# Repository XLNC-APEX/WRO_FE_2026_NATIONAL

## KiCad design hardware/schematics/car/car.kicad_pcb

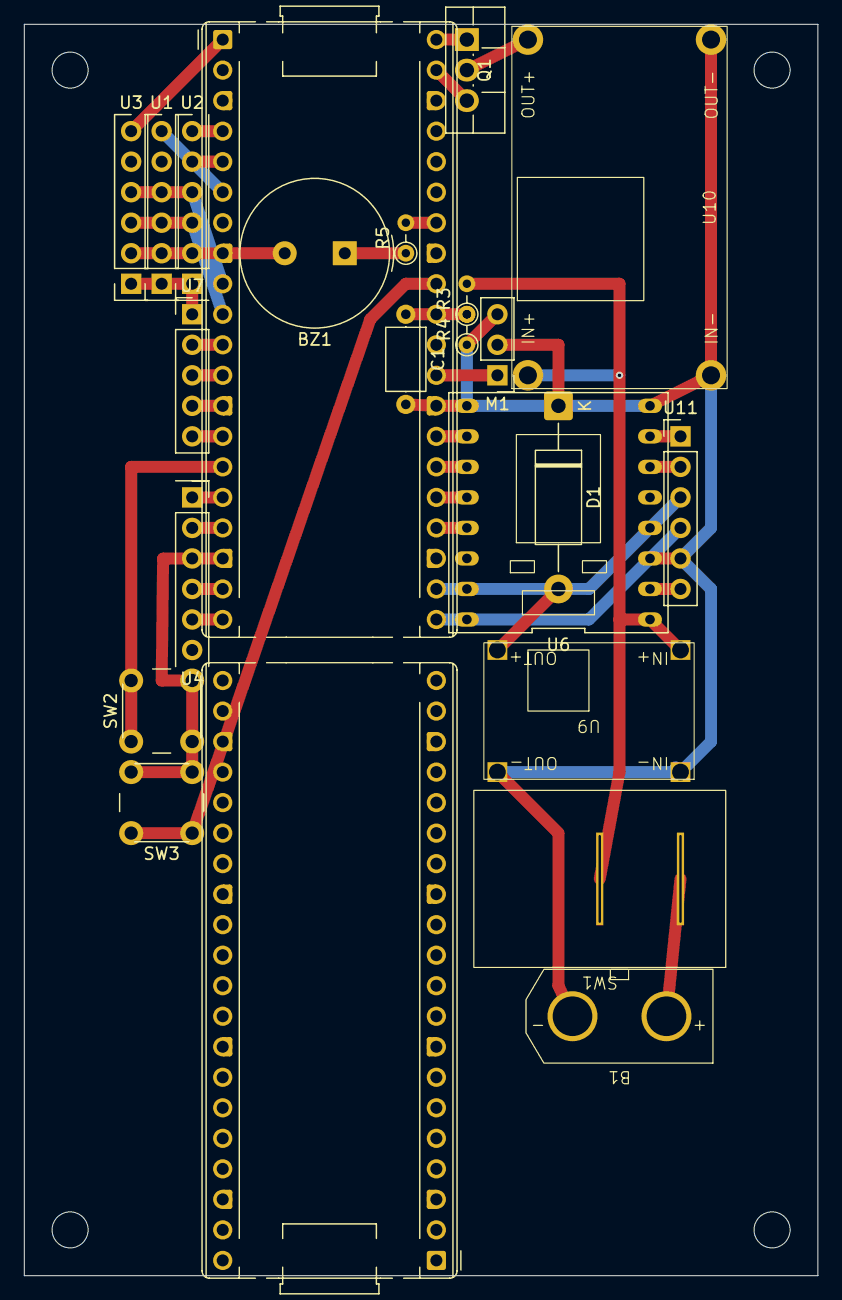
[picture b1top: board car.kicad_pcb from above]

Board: 12 copper layers, 66.0 x 104.1 mm, 23 parts (0 on the bottom side), 38 nets.

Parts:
A1, A1#2: RaspberryPi_Pico2; RaspberryPi_Pico_Common_THT
B1: XT60
BZ1: Buzzer; Buzzer_TDK_PS1240P02BT_D12.2mm_H6.5mm
C1: 1uF; C_Axial_L5.1mm_D3.1mm_P7.50mm_Horizontal
D1: 1N5824; D_DO-15_P15.24mm_Horizontal
M1: Motor_Servo; PinHeader_1x03_P2.54mm_Vertical
Q1: PMOS; TO-220F-3_Vertical
R3: 470k; R_Axial_DIN0204_L3.6mm_D1.6mm_P2.54mm_Vertical
R4: 100k; R_Axial_DIN0204_L3.6mm_D1.6mm_P2.54mm_Vertical
R5: 200; R_Axial_DIN0204_L3.6mm_D1.6mm_P2.54mm_Vertical
SW1: SW_SPST; SW_SPST_20.96mmx14.74mm
SW2, SW3: SW_Push; SW_PUSH_6mm_5.08mm
U1, U2, U3: VL53L0CXV0DH1; VL53L0_1XV2_PinHeader_1x06_P2.54mm_Vertical
U4: Pixy2; Pixy2_PinHeader_1x06_P2.54mm_Vertical
U6: TB6612FNG; TB6612FNG_Breakout_Sparkfun
U7: SparkFun OTOS; Sparkfun_OTOS_PinHeader_1x05_P2.54mm_Vertical
U9: Mini-360; Buck_Mini-360_2.54mm
U10: Mini-560; Buck_Mini-560_2.54mm
U11: JGA25-37x; JGA25-37x_PinHeader_1x06_P2.54mm_Vertical

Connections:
+3.3V: A1.36 (3V3), A1#2.36 (3V3), U1.11 (AVDD), U2.11 (AVDD), U3.11 (AVDD), U6.20 (VCC), U7.2 (3V3), U11.5 (VCC)
+5V: Q1.2 (D), U4.2 (5V), U10.4 (OUT+)
+6V: D1.2 (A), U9.4 (OUT+)
GND: A1.3 (GND), A1.8 (GND), A1.13 (GND), A1.18 (GND), A1.23 (GND), A1.28 (GND), A1.38 (GND), A1#2.3 (GND), A1#2.8 (GND), A1#2.13 (GND), A1#2.18 (GND), A1#2.23 (GND), A1#2.28 (GND), A1#2.38 (GND), B1.2 (-), BZ1.2 (-), C1.2, M1.3 (-), R4.1, SW2.2, SW3.2, U1.3 (GND), U2.3 (GND), U3.3 (GND), U4.6 (GND), U6.18 (GND), U7.1 (GND), U9.1 (IN-), U9.3 (OUT-), U10.1 (IN-), U10.3 (OUT-), U11.2 (GND)
unnamed: A1.1 (GPIO0), A1#2.1 (GPIO0), U3.5 (XSHUT)
unnamed: A1.2 (GPIO1), A1#2.2 (GPIO1), U3.7 (GPIO1)
unnamed: A1.4 (GPIO2), A1#2.4 (GPIO2), U2.5 (XSHUT)
unnamed: A1.5 (GPIO3), A1#2.5 (GPIO3), U2.7 (GPIO1)
unnamed: A1.6 (GPIO4), A1#2.6 (GPIO4), U1.5 (XSHUT)
unnamed: A1.7 (GPIO5), A1#2.7 (GPIO5), U1.7 (GPIO1)
unnamed: A1.9 (GPIO6), A1#2.9 (GPIO6), U1.9 (SDA), U2.9 (SDA), U3.9 (SDA)
unnamed: A1.10 (GPIO7), A1#2.10 (GPIO7), U1.10 (SCL), U2.10 (SCL), U3.10 (SCL)
unnamed: A1.11 (GPIO8), A1#2.11 (GPIO8), U7.3 (SDA)
unnamed: A1.12 (GPIO9), A1#2.12 (GPIO9), U7.4 (SCL)
unnamed: A1.14 (GPIO10), A1#2.14 (GPIO10), U7.5 (IO9)
unnamed: A1.15 (GPIO11), A1#2.15 (GPIO11), SW2.1
unnamed: A1.16 (GPIO12), A1#2.16 (GPIO12), U4.1 (MISO/RX)
unnamed: A1.17 (GPIO13), A1#2.17 (GPIO13), U4.7 (SPI_SS)
unnamed: A1.19 (GPIO14), A1#2.19 (GPIO14), U4.3 (SPI_SCK)
unnamed: A1.20 (GPIO15), A1#2.20 (GPIO15), U4.4 (MOSI/TX)
unnamed: A1.21 (GPIO16), A1#2.21 (GPIO16), U11.3 (C1)
unnamed: A1.22 (GPIO17), A1#2.22 (GPIO17), U11.4 (C2)
unnamed: A1.24 (GPIO18), A1#2.24 (GPIO18), U6.19 (STBY)
unnamed: A1.25 (GPIO19), A1#2.25 (GPIO19), U6.17 (BIN1)
unnamed: A1.26 (GPIO20), A1#2.26 (GPIO20), U6.16 (BIN2)
unnamed: A1.27 (GPIO21), A1#2.27 (GPIO21), U6.15 (PWMB)
unnamed: A1.29 (GPIO22), A1#2.29 (GPIO22), M1.1 (PWM)
unnamed: A1.31 (GPIO26_ADC0), A1#2.31 (GPIO26_ADC0), C1.1, R3.1, R4.2
unnamed: A1.32 (GPIO27_ADC1), A1#2.32 (GPIO27_ADC1), SW3.1
unnamed: A1.34 (GPIO28_ADC2), A1#2.34 (GPIO28_ADC2), R5.2
unnamed: A1.40 (VBUS), A1#2.40 (VBUS), Q1.1 (G)
unnamed: A1.39 (VSYS), A1#2.39 (VSYS), Q1.3 (S)
unnamed: B1.1 (+), SW1.1 (A)
unnamed: BZ1.1 (+), R5.1
unnamed: D1.1 (K), M1.2 (+)
unnamed: U6.11 (BO1), U11.1 (M1)
unnamed: U6.7 (BO2), U11.6 (M2)
VBAT: R3.2, SW1.2 (B), U6.24 (VM1), U9.2 (IN+), U10.2 (IN+)

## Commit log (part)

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2026-05-09 Initial, almost empty. Put placeholder files to add folder to git. Just started CAD
2026-05-09 CAD: add steering master sketch(depends on horizontal master). Create body(pad) of side steering plank.
2026-05-11 Change directory structure. Start KiCad schematic.
2026-05-11 Add https://github.com/ImplFerris/pico2-template.git template code. Make vscode rust-analyzer happy by setting compile target in .vscode/settings.json
2026-05-13 [SQUASH]: Just sync. Just testing, learning things.
2026-05-18 Upgrade and update dependencies
2026-05-18 Generalize: `extern crate embassy_rp as hal;` instead of `use`. Makes rust-analyzer suggest hal::smth too
2026-05-18 Add ssd1306 dependency with async feature
2026-05-18 Ssd1306Async usage as example of a good driver.
2026-05-18 Try to use vl53l0x asynchrounously
2026-05-25 Minor deps update
2026-05-25 Robot code README.md: run instructions
2026-05-26 Add GPL-3.0-or-later license to Cargo.toml
2026-05-29 [Schematic] Major work. Add: TOFs, Motor, servo, buzzer, ADC(WIP), level shifter. WIP
2026-05-29 [Schematic] Minor: Change datasheet and name to pico 2
2026-05-29 [Schematic] Servo: add schottky diode on power 1N5824
2026-05-30 [Schematic] Create Pixy2, OTOS, debug probe symbols. Add *.bak to .gitignore
2026-05-30 Use default background for symbols. Import our library into schematic project
2026-05-30 [Schematic] Add OTOS, Pixy, Debug probe, 2 buttons, fix voltage divider
2026-05-31 [Schematic] Create buck converters: mini 360, 560 symbols, footprints
2026-05-31 [Schematic] Add buck converters, put resitances on ADC.
2026-05-31 [Schematic] Major work: add many perfboard footprints, fix spi wrong
2026-06-02 [Schematic] mosfet fix. Use parasitic diode in our advantage
2026-06-02 [Schematic] add JGA25-37x symbol
2026-06-02 [Schematic] fix wrong footprint for JGA25-37x symbol
2026-06-02 [Schematic] use jga motor connector instead
2026-06-02 [Schematic] TB6612FNG breakout footprint
2026-06-02 [Schematic] schematic: use TB6612FNG breakout footprint
2026-06-02 [Schematic] create 4ch level shifter bss138 symbol and footprint
2026-06-02 [Schematic] Use simpler, smaller level shifter
2026-06-02 [Schematic] Fix super suboptimal connection for level shifter(was like cross thing)
2026-06-02 [Schematic] update pcb components
2026-06-02 [Schematic] Some pcb movings
2026-06-03 [Schematic] Remove level shifter. The pixy2 seems to have 3.3v outputs, maybe 3.3v tolerable input? Need testing.
2026-06-03 add servo adapter and holder cad
2026-06-03 Add xt60 symbol and footprint
2026-06-03 [Schematic] fix mosfet, add xt60
2026-06-03 [Schematic] Change button footprint. PCB: move around, connect easy things.
2026-06-03 [Schematic] Fix mini560 footprint. PCB: some moving.
2026-06-03 [Schematic] Add battery switch.
2026-06-03 [Schematic] Add battery switch to pcb.
2026-06-04 add motor adapter
2026-06-04 [Schematic] Fix footprints.
2026-06-04 [Schematic] pcb movings.
2026-06-04 [Schematic] Alternative schematic.
2026-06-04 [Schematic] PCB many things
2026-06-04 [Schematic] PCB moving again
2026-06-04 [Schematic] Add ADC cap, place underneath pico it and buzzer.
2026-06-04 [Schematic] Move a lot, fix mini560 footprint wrong size.
2026-06-04 [Schematic] Routed all.
2026-06-04 [Schematic] Minor fixes, finishing touches.
2026-06-04 [Schematic] Resize pcb. Ready for review
2026-06-04 [Schematic] Minor movements
2026-06-04 [Schematic] Major work: rewire schematic, route all perfboard, many fixes, additions.
2026-06-05 [Schematic] Add 200ohm R in series with buzzer to limit current.
2026-06-05 [CAD] Add otos adapter cad
2026-06-05 [Schematic] Add pcb viweing presets for reference when soldering.
2026-06-05 [Schematic] Fix TB6612FNG by one wider fotoprint.
2026-06-05 [Schematic] reroute the fixed footprint.
2026-06-05 [Schematic] Move left by one motor connector.
2026-06-06 [Schematic] Minor change: add leyer for preset viewing in pcb.
2026-06-06 encoder working. TODO: test motor. Use driver for motor with encoder
2026-06-06 Add motor actually. Works. TODO: PIDF, better pio encoder
2026-06-06 Update test motor for new pins, our board. Tested, works
2026-06-06 [CAD] add tof sensor and pixy2 adapter
2026-06-06 Working async with single sensor
2026-06-06 New, refactored
2026-06-06 2 tof on one i2c bus working
2026-06-06 Updated for our board
2026-06-06 Averaging ADC test
2026-06-08 [CAD] add perfboard and battery holder
2026-06-08 [Schematic] moved mini-360 to replace it and not clean the through holes.
2026-06-08 [Code] Update deps.
2026-06-08 Use driver from git, not from local path
2026-06-08 Otos version test. Success! Version { hw: 17, fw: 16 }
2026-06-08 Test updated driver. Adds scalar, sd, config.
2026-06-08 Tested claibration, reset, pos
2026-06-08 Simple servo test
2026-06-08 Update to use buttons too.
2026-06-09 Find extremes
2026-06-10 Pixy2 SPI works without level shifter!
2026-06-10 Use pixy2 WIP driver to get version
2026-06-10 Change pinout to board
2026-06-10 Get version success
2026-06-10 Add init almost all components code(forgot buttons). Does not crash)))
2026-06-10 Fix motor: prevent stby pin var dropping. Add 2 buttons, Add example embassy task
2026-06-11 Add potential holes in perfboard
2026-06-11 Add get_blocks test example. Works
2026-06-11 Minor comment edit
2026-06-11 I hate vl53l0x and this driver for it
2026-06-13 [CAD] Add new servo adapter
2026-06-13 [CAD] Update servo adapter 3mf file
2026-06-13 [CAD] add servo-holder
2026-06-13 [CAD] Revert to older otos holder version
2026-06-13 [CAD] Otos, make space for it and pin headers to fit
2026-06-13 [CAD] Improve perfboard holder. Changes in motor, otos adapter(printed), tof
2026-06-13 [Schematic] PCB: Change holes and boundary to real. Add second pico(just visual)
2026-06-14 [Code] Added watchdog, buzzer song player to devices. Updated deps(fixes pixy init)
2026-06-14 [Code] Embed.toml: rename RP2350 -> RP235x: removes wildcard warning from cargo embed.
2026-06-14 [CAD] Update the working motor adapter
2026-06-14 [Code] fix servo wrong angle dir. Make motor_servo_play try go lateral
2026-06-14 [Code] Otos test
2026-06-15 [Code] fixed tof error
2026-06-15 [Code] rename tof sensors
2026-06-18 Add schematic image/screenshot.
2026-06-18 Place schematic image into README.md
2026-06-21 [Code] Reset in btn press task
2026-06-23 comment out pixy2 init
2026-06-23 [Code] Update deps
2026-06-23 [Code] Comment pixy, cleanup main.rs
2026-06-24 [Code] WIP PurePursuit impl structure. No logic yet
2026-06-24 [Code] PurePursuit: impl simple logic. Need to impl get TP yet
2026-06-24 [Code] PurePursuit: impl get_target_point(&mut self, ld: f32) -> Point2<f32>
2026-06-24 [Code] PurePursuit: make it theoretically working
2026-06-24 [Code] PurePursuit: Broken: make it more theoretically working
2026-06-25 [Code] PurePursuit: Just sync some debugging
2026-06-29 [Code] fix vl53l0x compiling, update deps, add --dev gnuplot
2026-06-29 [Code] fix deps after rebase
